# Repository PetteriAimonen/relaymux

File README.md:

# USB Relay Mux box

This repository contains hardware and firmware for a USB Relay Mux that has two independent halves,
each of which multiplexes a pair of signals to four channels. It is designed for use in automatic
testing, for example to switch input signals to multimeter or to change polarity of a power supply.

[**Schematic**](pcb/images/relaymux.pdf) - [**BOM**](pcb/gerbers/bom-generic.csv) - [**Gerbers**](pcb/gerbers/)

## Design

Many of the cheap USB relay boards are designed for switching large currents, and not for lab usage.
They have several shortcomings:

* Poor quality relays, which have varying amount of resistance when switching small currents.
* Weird custom protocol with no feedback from device.
* Excessive current draw from USB bus when all relays are activated.

This project implements the standard SCPI command set and uses higher quality [Panasonic TQ2SA-5V](https://na.industrial.panasonic.com/products/relays-contactors/mechanical-signal-relays/lineup/signal-relays/series/119572/model/119942) relays.

## Specifications

* Switching time: 10 ms
* Maximum current and voltage:
  * up to 30 Vrms: AC 1 A or DC 2 A
  * up to 125 Vrms: AC or DC 0.5 A
* Parasitic capacitance: 40 pF each signal to GND
* Wetting current: 10 µA
* Contact resistance: 50 mohm typical, max 150 mohm
* Power supply: USB 5V 300mA
* Control: SCPI over USB CDC-ACM serial port

## SCPI command set

* `*IDN?`: Query model name and serial number
* `OPEN @(1,2,5:8)`: Open (disconnect) one or multiple relay channels
* `CLOSE @(1,5)`: Close (connect) one or multiple relay channels
* `CLOSE? (@1)`: Query whether a specific channel is closed
* `CLOSE:STATE?`: Return a list of all closed channels
* `OPEN:ALL`: Open all channels
* `SET 255`: Set channel states as 8-bit integer, break-before-make
* `SET:MBB 255`: Set channel states as 8-bit integer, make-before-break
* `GET?`: Get channel states as 8-bit integer

The commands follow "Signal Switchers" instrument category of SCPI 1999 standard.

All commands wait for relay switching, so consecutive instructions will follow correct make/break sequencing.

## Parts

| Part            | Info                            | Approx. cost (without taxes) |
|-----------------|---------------------------------|--------------|
| PCB             | 120x100 mm, [gerbers](pcb/gerbers) | 8 EUR     |
| Components      | [Listed in BOM](pcb/gerbers/bom-generic.csv) | 18 EUR |
| Binding posts   | 20 pcs, 5 mm mounting hole | 10 EUR |
| Enclosure       | Hammond [1550MBK](https://www.hammfg.com/part/1550MBK) | 15 EUR |
| **Total**           | | **51 EUR**|

The PCB is designed for mounting the binding posts directly with a nut to the 5 mm hole.
How well this works depends on the specific connector model.
If needed, the hole can be drilled larger without damage to the traces, and a soldering
area is provided in case there is no electrical contact through the screw.
Some solder is a good idea in any case to prevent it from the connector spinning in the hole.
Cheapest binding posts can be found on eBay, but some of them lack a hole for a wire.

The PCB replaces the original lid of the enclosure. A small notch needs to be filed for the USB-C connector to fit through.

## Firmware

STM32F042 firmware is based on STM32Cube USB-CDC library and [scpi-parser](https://github.com/j123b567/scpi-parser) library.

It can be built using [PlatformIO](https://platformio.org):

    pio run
    ...
    RAM:   [=====     ]  52.5% (used 3224 bytes from 6144 bytes)
    Flash: [========  ]  80.3% (used 26300 bytes from 32768 bytes)

The board can be programmed through USB DFU protocol using STM32 built-in bootloader.
The bootloader is activated by holding down `Clear` button while plugging in the cable.

## License

The electronics design is licensed under [CC-BY-4.0](https://creativecommons.org/licenses/by/4.0/deed.fi).
Suggested attribution format for derivative designs:

    Based on USB Relay Mux by Petteri Aimonen, https://github.com/PetteriAimonen/relaymux/

The firmware is licensed under [BSD 2-Clause license](LICENSE).

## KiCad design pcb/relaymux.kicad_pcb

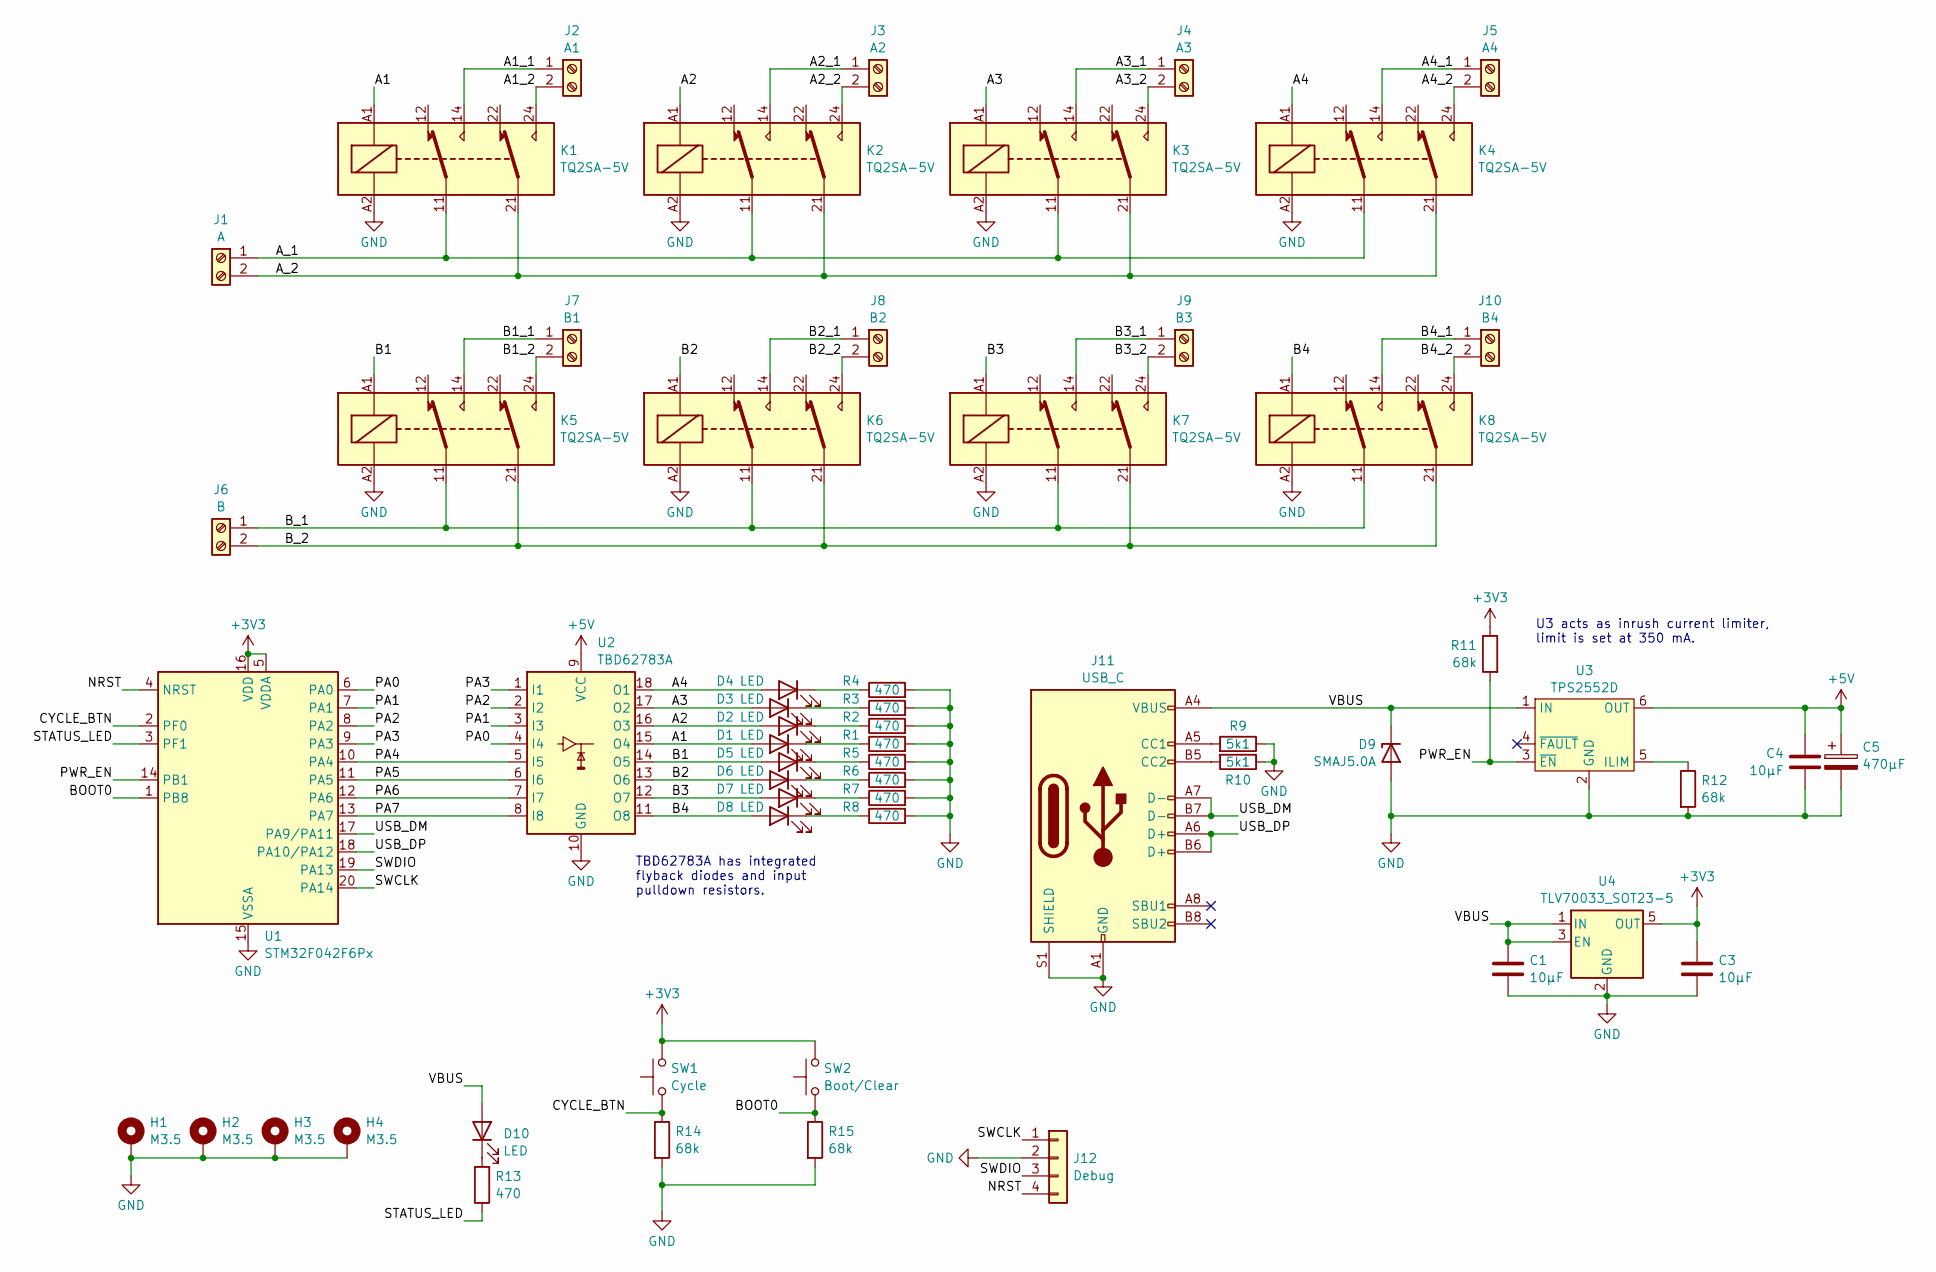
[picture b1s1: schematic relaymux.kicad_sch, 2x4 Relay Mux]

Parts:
C1, C3, C4: 10µF; C_0805_2012Metric; MPN CL21A106KAYNNNE; LCSC C15850
C5: 470µF; CP_Elec_10x10; MPN UWD1E471MCL1GS; LCSC C251022
D1, D2, D3, D4, D5, D6, D7, D8, D10: LED; LED_LTST-C230; MPN LTST-C230KGKT; LCSC C125106
D9: SMAJ5.0A; D_SMA; MPN SMAJ5.0A; LCSC C2925443
H1, H2, H3, H4: M3.5; MountingHole_4mm_Pad
J1: A; Binding_Post_Pair
J2: A1; Binding_Post_Pair_120deg
J3: A2; Binding_Post_Pair_120deg
J4: A3; Binding_Post_Pair_120deg
J5: A4; Binding_Post_Pair_120deg
J6: B; Binding_Post_Pair
J7: B1; Binding_Post_Pair_60deg
J8: B2; Binding_Post_Pair_60deg
J9: B3; Binding_Post_Pair_60deg
J10: B4; Binding_Post_Pair_60deg
J11: USB_C; USB_C_Receptacle_XKB_U262-16XN-4BVC11; MPN USB4110; LCSC C319148
J12: Debug; Pads_1x04_P2.54mm_Vertical
K1, K2, K3, K4, K5, K6, K7, K8: TQ2SA-5V; Relay_TQ2SA; MPN TQ2SA-5V; LCSC C2858038
R1, R2, R3, R4, R5, R6, R7, R8, R13: 470; R_0805_2012Metric; MPN Generic 470 ohm 0805; LCSC C17710
R9, R10: 5k1; R_0805_2012Metric; MPN Generic 5.1kohm 0805; LCSC C27834
R11, R12, R14, R15: 68k; R_0805_2012Metric; MPN Generic 68kohm 0805; LCSC C17801
SW1: Cycle; SW_320E11; MPN 320E11BLK; LCSC C273375
SW2: Boot/Clear; SW_320E11; MPN 320E11BLK; LCSC C273375
U1: STM32F042F6Px; TSSOP-20_4.4x6.5mm_P0.65mm; MPN STM32F042F6P6; LCSC C2969989
U2: TBD62783A; SOP-18_7x12.5mm_P1.27mm; MPN TBD62783AFG,EL; LCSC C97745
U3: TPS2552D; SOT-23-6; MPN TPS2552DBVR; LCSC C46506
U4: TLV70033_SOT23-5; SOT-23-5; MPN TLV70033DDCR; LCSC C11337

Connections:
+3V3: C3.1, R11.1, SW1.2, SW2.2, U1.5 (VDDA), U1.16 (VDD), U4.5 (OUT)
+5V: C4.1, C5.1, U2.9 (VCC), U3.6 (OUT)
/A1: D1.2 (A), K1.A1, U2.15 (O4)
/A1_1: J2.1, K1.14
/A1_2: J2.2, K1.24
/A2: D2.2 (A), K2.A1, U2.16 (O3)
/A2_1: J3.1, K2.14
/A2_2: J3.2, K2.24
/A3: D3.2 (A), K3.A1, U2.17 (O2)
/A3_1: J4.1, K3.14
/A3_2: J4.2, K3.24
/A4: D4.2 (A), K4.A1, U2.18 (O1)
/A4_1: J5.1, K4.14
/A4_2: J5.2, K4.24
/A_1: J1.1, K1.11, K2.11, K3.11, K4.11
/A_2: J1.2, K1.21, K2.21, K3.21, K4.21
/B1: D5.2 (A), K5.A1, U2.14 (O5)
/B1_1: J7.1, K5.14
/B1_2: J7.2, K5.24
/B2: D6.2 (A), K6.A1, U2.13 (O6)
/B2_1: J8.1, K6.14
/B2_2: J8.2, K6.24
/B3: D7.2 (A), K7.A1, U2.12 (O7)
/B3_1: J9.1, K7.14
/B3_2: J9.2, K7.24
/B4: D8.2 (A), K8.A1, U2.11 (O8)
/B4_1: J10.1, K8.14
/B4_2: J10.2, K8.24
/BOOT0: R15.1, SW2.1, U1.1 (PB8)
/B_1: J6.1, K5.11, K6.11, K7.11, K8.11
/B_2: J6.2, K5.21, K6.21, K7.21, K8.21
/CYCLE_BTN: R14.1, SW1.1, U1.2 (PF0)
/NRST: J12.4, U1.4 (NRST)
/PA0: U1.6 (PA0), U2.4 (I4)
/PA1: U1.7 (PA1), U2.3 (I3)
/PA2: U1.8 (PA2), U2.2 (I2)
/PA3: U1.9 (PA3), U2.1 (I1)
/PA4: U1.10 (PA4), U2.5 (I5)
/PA5: U1.11 (PA5), U2.6 (I6)
/PA6: U1.12 (PA6), U2.7 (I7)
/PA7: U1.13 (PA7), U2.8 (I8)
/PWR_EN: R11.2, U1.14 (PB1), U3.3 (~EN)
/STATUS_LED: R13.1, U1.3 (PF1)
/SWCLK: J12.1, U1.20 (PA14)
/SWDIO: J12.3, U1.19 (PA13)
/USB_DM: J11.A7 (D-), J11.B7 (D-), U1.17 (PA9/PA11)
/USB_DP: J11.A6 (D+), J11.B6 (D+), U1.18 (PA10/PA12)
/VBUS: C1.1, D9.1 (K), D10.2 (A), J11.A4 (VBUS), J11.A9 (VBUS), J11.B4 (VBUS), J11.B9 (VBUS), U3.1 (IN), U4.1 (IN), U4.3 (EN)
GND: C1.2, C3.2, C4.2, C5.2, D9.2 (A), H1.1, H2.1, H3.1, H4.1, J11.A1 (GND), J11.A12 (GND), J11.B1 (GND), J11.B12 (GND), J11.S1 (SHIELD), J12.2, K1.A2, K2.A2, K3.A2, K4.A2, K5.A2, K6.A2, K7.A2, K8.A2, R1.2, R2.2, R3.2, R4.2, R5.2, R6.2, R7.2, R8.2, R9.1, R10.1, R12.2, R14.2, R15.2, U1.15 (VSSA), U2.10 (GND), U3.2 (GND), U4.2 (GND)
unnamed: D1.1 (K), R1.1
unnamed: D2.1 (K), R2.1
unnamed: D3.1 (K), R3.1
unnamed: D4.1 (K), R4.1
unnamed: D5.1 (K), R5.1
unnamed: D6.1 (K), R6.1
unnamed: D7.1 (K), R7.1
unnamed: D8.1 (K), R8.1
unnamed: D10.1 (K), R13.2
unnamed: J11.A5 (CC1), R9.2
unnamed: J11.B5 (CC2), R10.2
unnamed: R12.1, U3.5 (ILIM)

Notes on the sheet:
U3 acts as inrush current limiter, limit is set at 350 mA.
TBD62783A has integrated flyback diodes and input pulldown resistors.

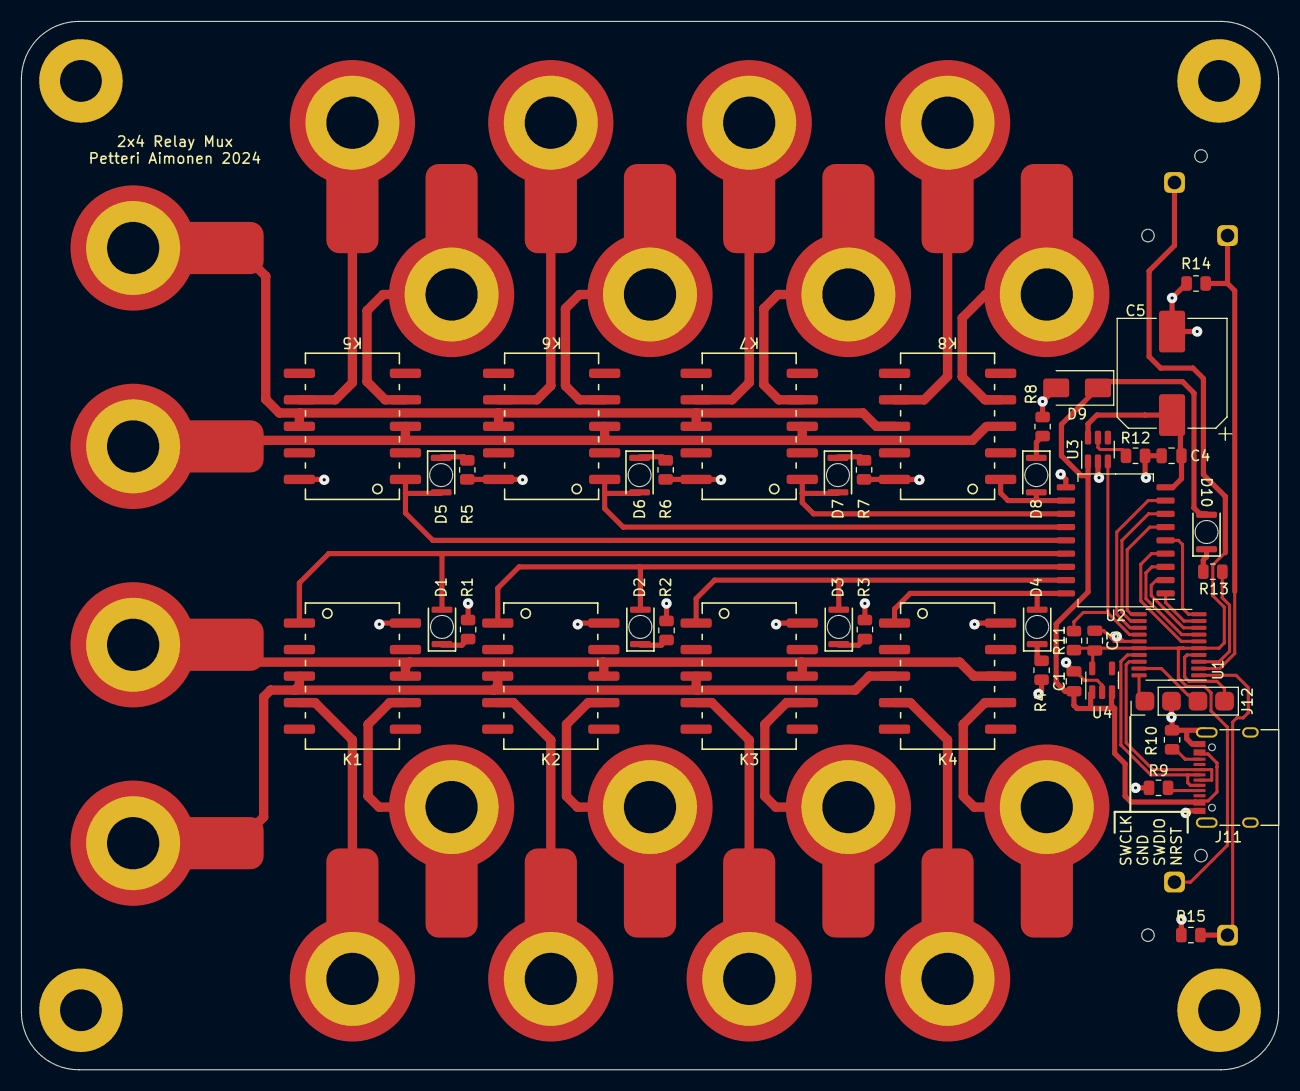
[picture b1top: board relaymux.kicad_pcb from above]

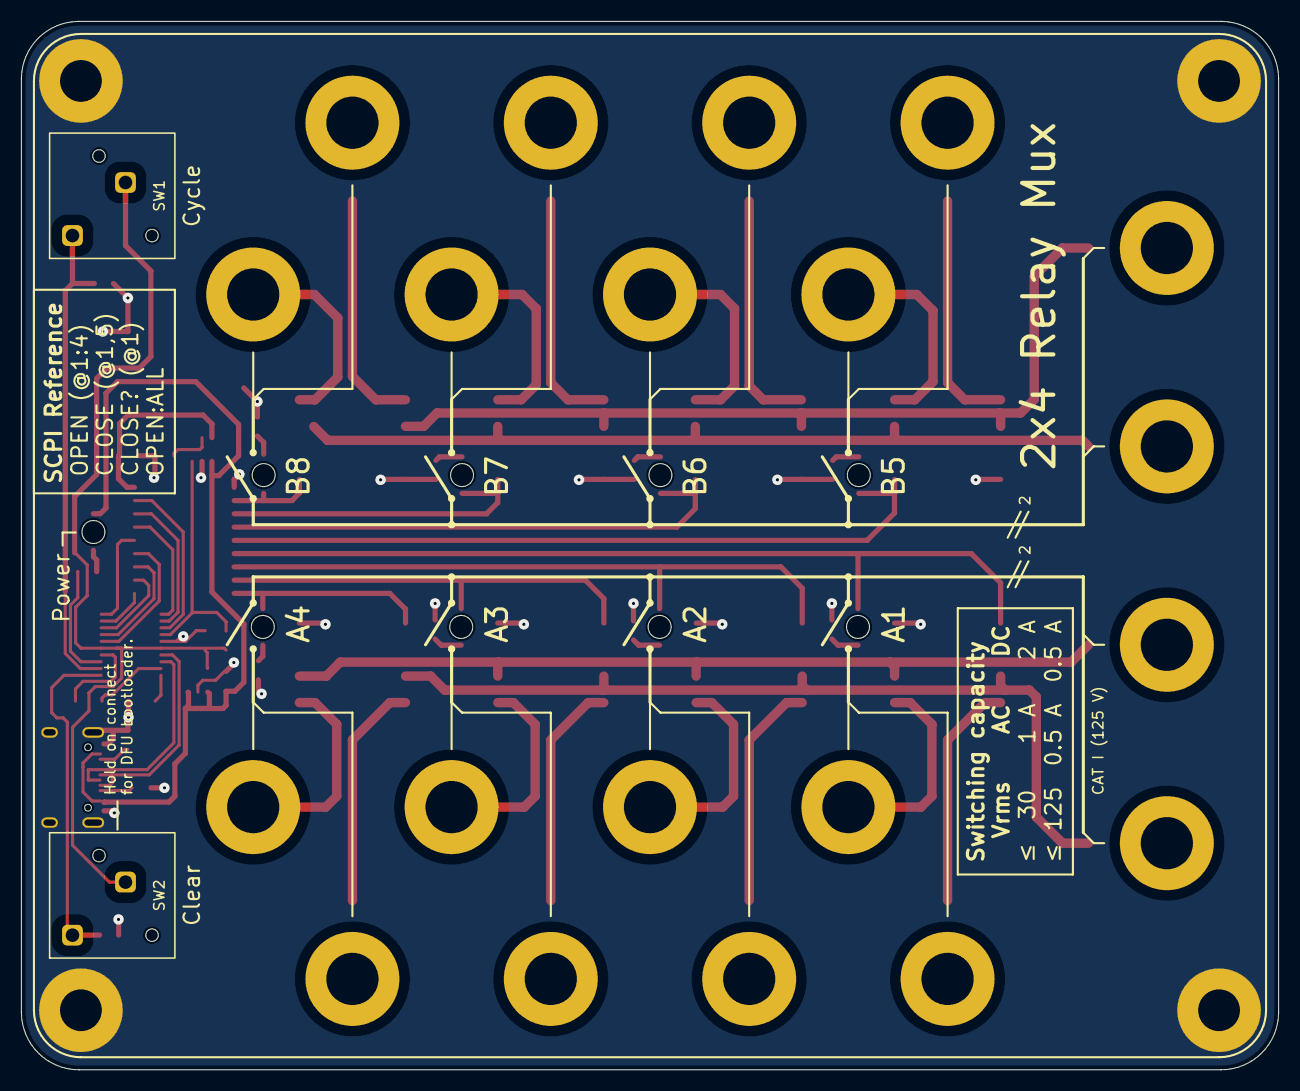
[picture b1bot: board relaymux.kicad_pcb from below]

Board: 2 copper layers, 120.4 x 100.4 mm, 59 parts (2 on the bottom side), 61 nets.

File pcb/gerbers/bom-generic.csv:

"Reference","Value","Footprint","LCSC","MPN","Qty"
"C1, C3, C4","10µF","Capacitor_SMD:C_0805_2012Metric","C15850","CL21A106KAYNNNE","3"
"C5","470µF","Capacitor_SMD:CP_Elec_10x10","C251022","UWD1E471MCL1GS","1"
"D1-D8, D10","LED","relaymux:LED_LTST-C230","C125106","LTST-C230KGKT","9"
"D9","SMAJ5.0A","Diode_SMD:D_SMA","C2925443","SMAJ5.0A","1"
"H1-H4","M3.5","MountingHole:MountingHole_4mm_Pad","","","4"
"J1","A","relaymux:Binding_Post_Pair","","","1"
"J2","A1","relaymux:Binding_Post_Pair_120deg","","","1"
"J3","A2","relaymux:Binding_Post_Pair_120deg","","","1"
"J4","A3","relaymux:Binding_Post_Pair_120deg","","","1"
"J5","A4","relaymux:Binding_Post_Pair_120deg","","","1"
"J6","B","relaymux:Binding_Post_Pair","","","1"
"J7","B1","relaymux:Binding_Post_Pair_60deg","","","1"
"J8","B2","relaymux:Binding_Post_Pair_60deg","","","1"
"J9","B3","relaymux:Binding_Post_Pair_60deg","","","1"
"J10","B4","relaymux:Binding_Post_Pair_60deg","","","1"
"J11","USB_C","Connector_USB:USB_C_Receptacle_XKB_U262-16XN-4BVC11","C319148","USB4110","1"
"J12","Debug","relaymux:Pads_1x04_P2.54mm_Vertical","","","1"
"K1-K8","TQ2SA-5V","relaymux:Relay_TQ2SA","C2858038","TQ2SA-5V","8"
"R1-R8, R13","470","Resistor_SMD:R_0805_2012Metric","C17710","Generic","9"
"R9, R10","5k1","Resistor_SMD:R_0805_2012Metric","C27834","Generic","2"
"R11, R12, R14, R15","68k","Resistor_SMD:R_0805_2012Metric","C17801","Generic","4"
"SW1","Cycle","relaymux:SW_320E11","C273375","320E11BLK","1"
"SW2","Boot/Clear","relaymux:SW_320E11","C273375","320E11BLK","1"
"U1","STM32F042F6Px","Package_SO:TSSOP-20_4.4x6.5mm_P0.65mm","C2969989","STM32F042F6P6","1"
"U2","TBD62783A","Package_SO:SOP-18_7x12.5mm_P1.27mm","C97745","TBD62783AFG,EL","1"
"U3","TPS2552D","Package_TO_SOT_SMD:SOT-23-6","C46506","TPS2552DBVR","1"
"U4","TLV70033_SOT23-5","Package_TO_SOT_SMD:SOT-23-5","C11337","TLV70033DDCR","1"

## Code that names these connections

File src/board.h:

// GPIO mapping for 2x4 relay mux board

#pragma once

#include <stm32f042x6.h>
#include <stm32f0xx_hal.h>
#include <stdbool.h>

#define CYCLE_BTN_PORT  GPIOF
#define CYCLE_BTN_PIN   GPIO_PIN_0

#define CLEAR_BTN_PORT  GPIOB
#define CLEAR_BTN_PIN   GPIO_PIN_8

#define BTN_DEBOUNCE_TIME_MS 100

#define STATUS_LED_PORT GPIOF
#define STATUS_LED_PIN  GPIO_PIN_1
#define STATUS_LED_ON() STATUS_LED_PORT->BRR = STATUS_LED_PIN
#define STATUS_LED_OFF() STATUS_LED_PORT->BSRR = STATUS_LED_PIN

#define PWR_EN_PORT     GPIOB
#define PWR_EN_PIN      GPIO_PIN_1

#define RELAY_PORT      GPIOA
#define RELAY_PIN_SHIFT 0
#define RELAY_COUNT     8
#define RELAY_MASK      0xFF
#define RELAY_OPERATE_DELAY_MS  10
#define RELAY_RELEASE_DELAY_MS  10

void board_init();

void set_relay_pwr(bool enable);
void close_relays(uint32_t channels);
void open_relays(uint32_t channels);
uint32_t relays_get_state();

#define BTN_CYCLE   0x01
#define BTN_CLEAR   0x02

// Returns button presses exactly once per press-and-release
uint32_t read_buttons();

// Simple logging to memory ringbuffer
void board_log(const char *data);

// Serial number for the device (from STM32 unique ID)
const char *board_serialnumber();

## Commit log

2024-02-15 First revision
2024-02-27 Reorganize directories
2024-03-05 First version of firmware
2024-03-05 Smaller holes for reverse mount LEDs
2024-03-26 Add readme, BOM
